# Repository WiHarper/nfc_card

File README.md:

# NFC Energy-Harvesting PCB Business Card with an MCU

Like most business cards, this one doesn’t have a battery. When it’s tapped against a phone, though, 21 LEDs start an animation, powered just by NFC.

**Find more information at [wlsn.ee/nfc](https://wlsn.ee/nfc).**

## Details

* MCU: ATtiny816 
* NFC Chip: NXP NTAG I2C Plus
* Antenna: Custom rectangular coil tuned to ~2.75 µH
* Display: 21 Charlieplexed LEDs
* Dimensions: Payment card form factor

## Repository Layout

* `hardware/` - KiCad 9.0 schematic files/PCB layout files and 3D models
* `software/` - firmware and KiPython script
* `gallery/` - photos/video of card

## Programming

The ATtiny is flashed over UPDI; its clock speed should be set to 1 MHz. The NFC chip is formatted and written using [NXP Tagwriter](https://play.google.com/store/apps/details?id=com.nxp.nfc.tagwriter&hl=en_US). Energy harvesting is enabled by default, and it is easy to add vCard records or a website link.

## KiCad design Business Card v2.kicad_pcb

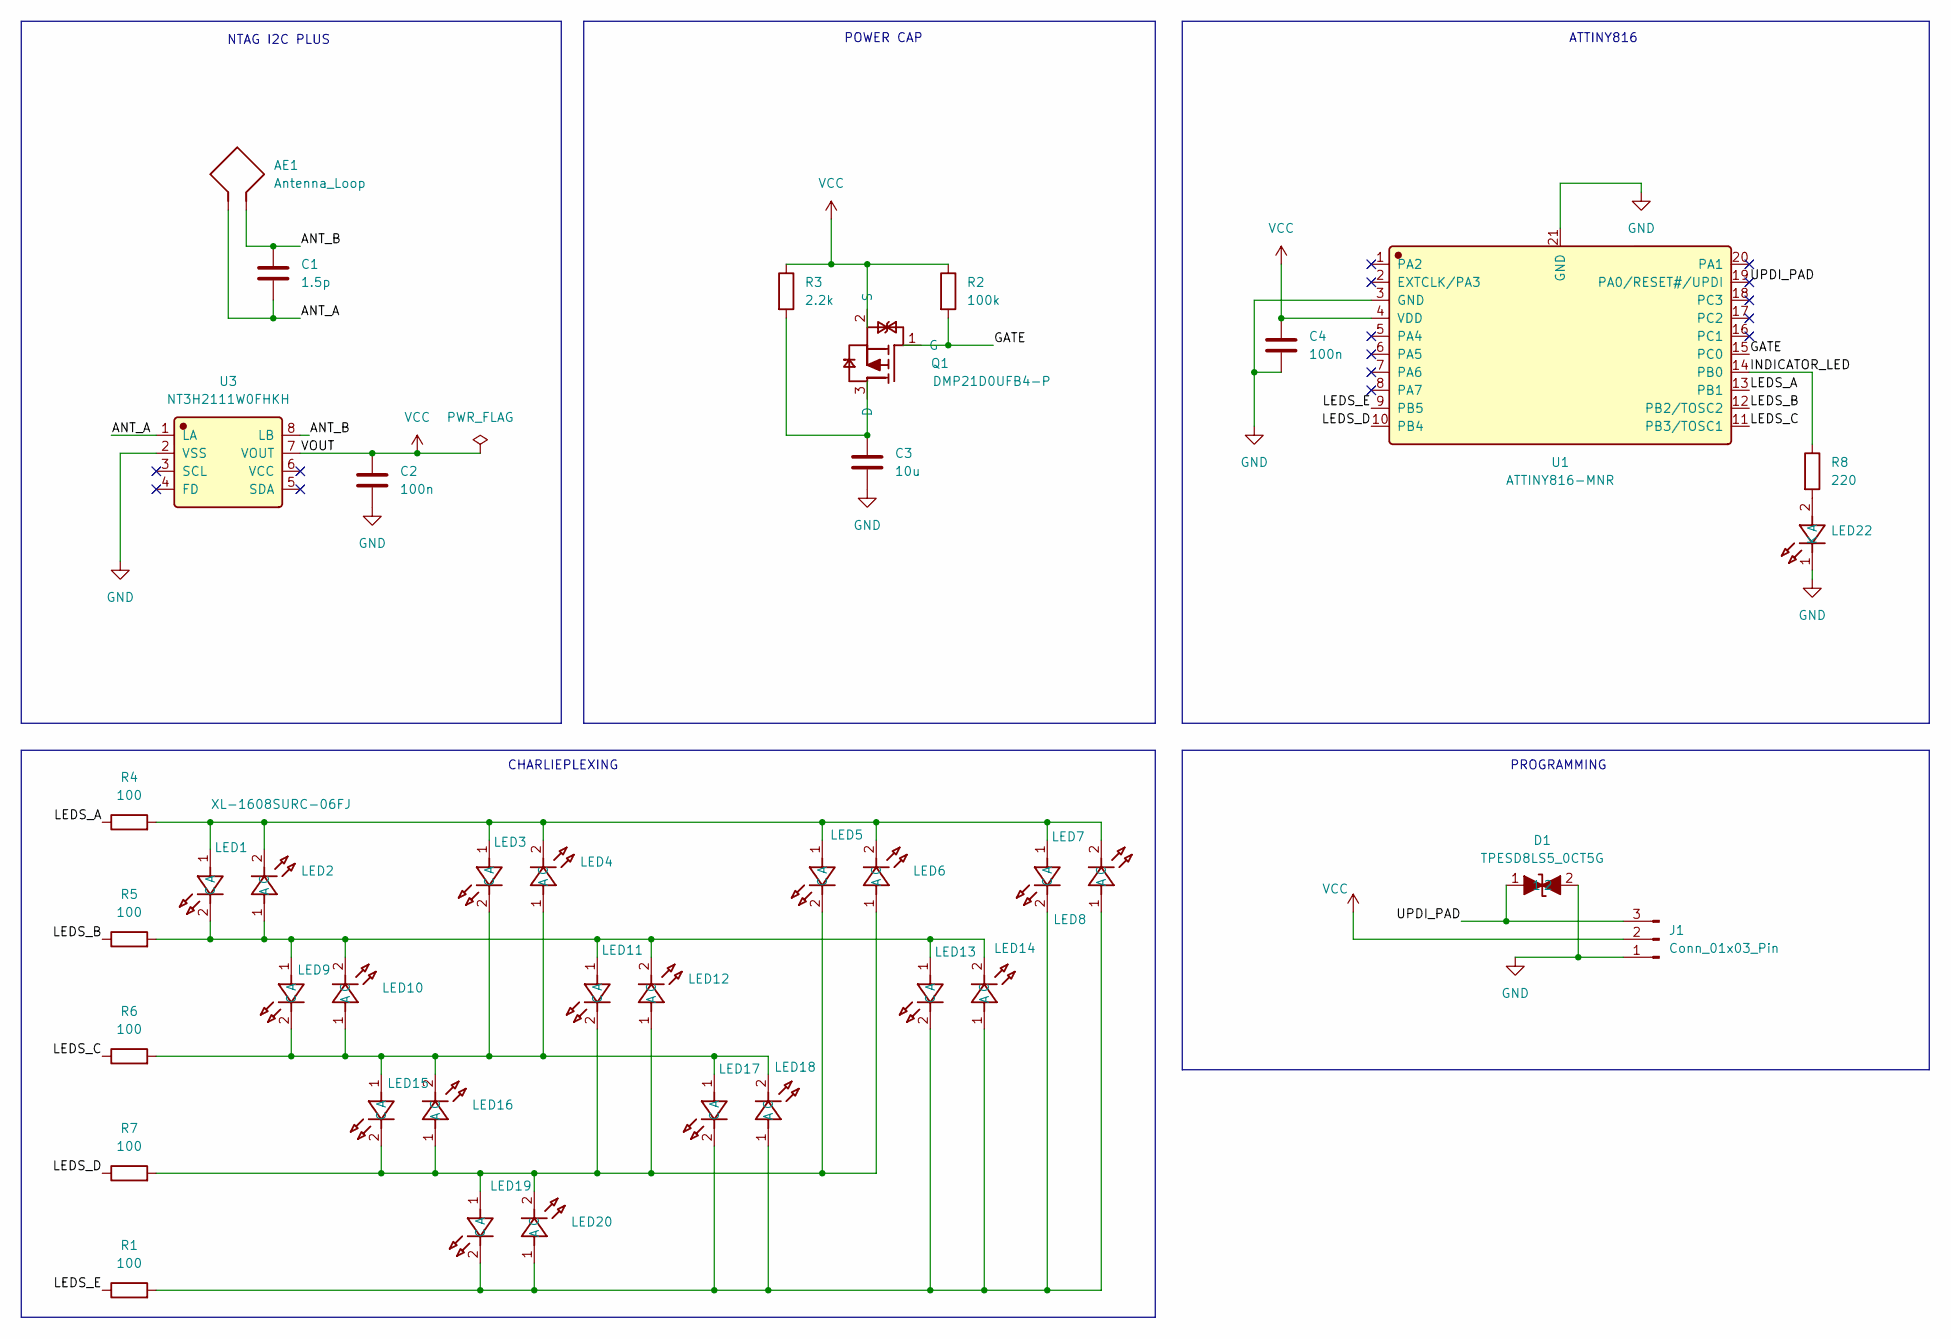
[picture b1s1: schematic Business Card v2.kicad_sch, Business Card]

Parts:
AE1: Antenna_Loop; Antenna V3
C1: 1.5p; C_0402_1005Metric; LCSC C1639
C2, C4: 100n; C_0402_1005Metric; LCSC C1525
C3: 10u; C_0402_1005Metric; LCSC C15525
D1: TPESD8LS5_0CT5G; TPESD8L3_3CT5G; Manufacturer Part TPESD8LS5.0CT5G; LCSC C2827551
J1: Conn_01x03_Pin; Offset UPDI
LED1, LED2, LED3, LED4, LED5, LED6, LED7, LED8, LED9, LED10, LED11, LED12, LED13, LED14, LED15, LED16, LED17, LED18, LED19, LED20: XL-1608SURC-06FJ; Manufacturer Part XL-1608SURC-06FJ; LCSC C7371900
LED22: XL-1608UYC-06FJ; Manufacturer Part XL-1608UYC-06FJ; LCSC C7371901
Q1: DMP21D0UFB4-P; Manufacturer Part DMP21D0UFB4-P; LCSC C2905648
R1, R5, R6, R7: 100; R_0402_1005Metric; LCSC C25076
R2: 100k; R_0402_1005Metric; LCSC C25741
R3: 2.2k; R_0402_1005Metric; LCSC C25879
R4: 100; R_0402_1005Metric
R8: 220; R_0402_1005Metric; LCSC C25091
U1: ATTINY816-MNR; Manufacturer Part ATTINY816-MNR; LCSC C2052778
U3: NT3H2111W0FHKH; Manufacturer Part NT3H2111W0FHKH; LCSC C710403

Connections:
/ANT_A: AE1.1, C1.2, U3.1 (LA)
/ANT_B: AE1.2, C1.1, U3.8 (LB)
/GATE: Q1.1 (G), R2.2, U1.15 (PC0)
/INDICATOR_LED: R8.1, U1.14 (PB0)
/LEDS_A: R4.1, U1.13 (PB1)
/LEDS_B: R5.1, U1.12 (PB2/TOSC2)
/LEDS_C: R6.1, U1.11 (PB3/TOSC1)
/LEDS_D: R7.1, U1.10 (PB4)
/LEDS_E: R1.1, U1.9 (PB5)
/UPDI_PAD: D1.1, J1.3, U1.19 (PA0/RESET#/UPDI)
GND: C2.2, C3.2, C4.2, D1.2, J1.1, LED22.1 (K), U1.3 (GND), U1.21 (GND), U3.2 (VSS)
unnamed: LED1.1 (A), LED2.2 (C), LED3.1 (A), LED4.2 (C), LED5.1 (A), LED6.2 (C), LED7.2 (C), LED8.1 (A), R4.2
unnamed: LED1.2 (C), LED2.1 (A), LED9.1 (A), LED10.2 (C), LED11.1 (A), LED12.2 (C), LED13.1 (A), LED14.2 (C), R5.2
unnamed: LED3.2 (C), LED4.1 (A), LED9.2 (C), LED10.1 (A), LED15.1 (A), LED16.2 (C), LED17.1 (A), LED18.2 (C), R6.2
unnamed: LED5.2 (C), LED6.1 (A), LED11.2 (C), LED12.1 (A), LED15.2 (C), LED16.1 (A), LED19.1 (A), LED20.2 (C), R7.2
unnamed: LED7.1 (A), LED8.2 (C), LED13.2 (C), LED14.1 (A), LED17.2 (C), LED18.1 (A), LED19.2 (C), LED20.1 (A), R1.2
unnamed: LED22.2 (A), R8.2
unnamed: C3.1, Q1.3 (D), R3.2
VCC: C2.1, C4.1, J1.2, Q1.2 (S), R2.1, R3.1, U1.4 (VDD), U3.7 (VOUT)

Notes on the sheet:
NTAG I2C PLUS
POWER CAP
ATTINY816
PROGRAMMING
CHARLIEPLEXING

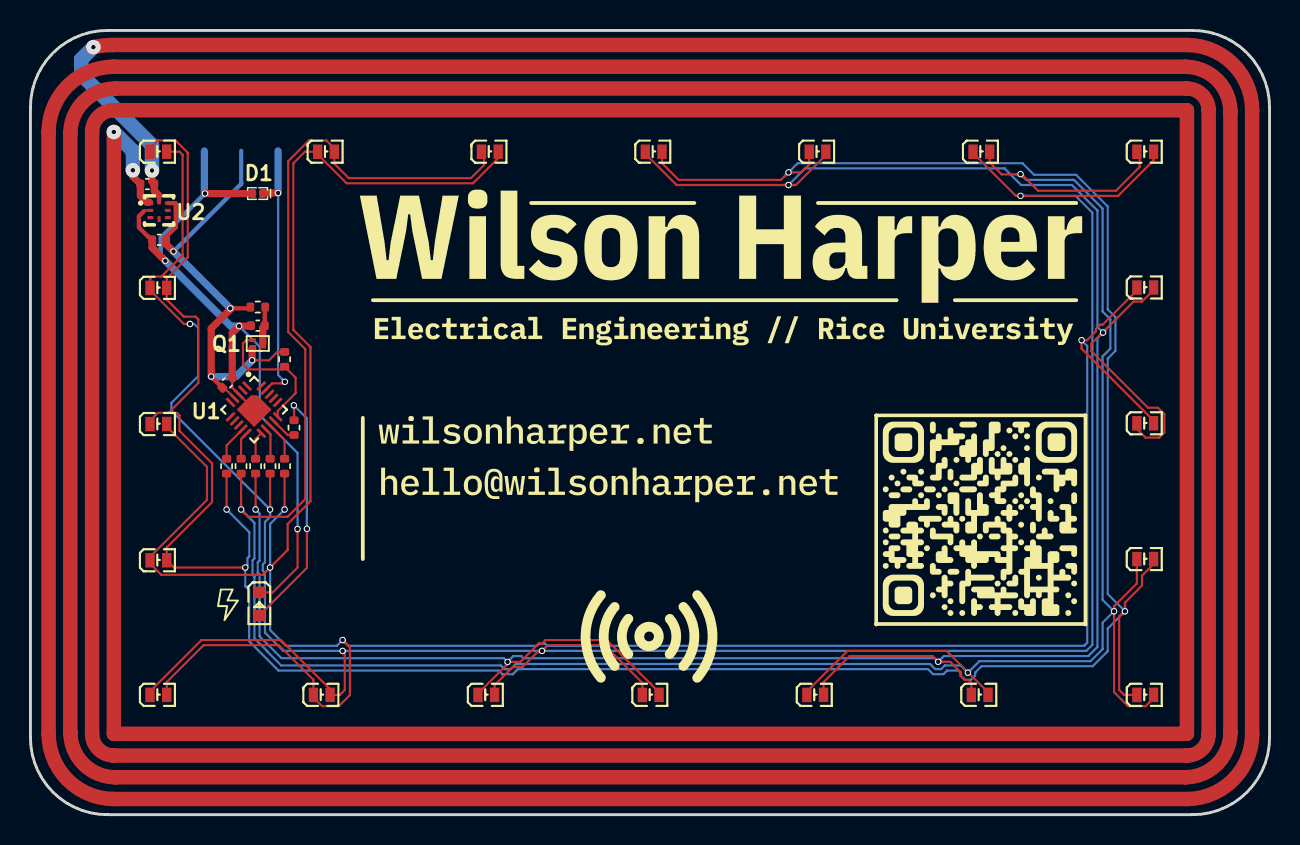
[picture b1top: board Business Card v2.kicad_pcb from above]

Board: 2 copper layers, 85.4 x 54.1 mm, 39 parts (1 on the bottom side), 19 nets.

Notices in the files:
Business Card v2.kicad_pcb:
Liscenced under GPL v3.0
Business Card v2.kicad_sch:
Liscenced under GPL Vx.x
